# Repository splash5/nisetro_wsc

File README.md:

# nisetro_wsc
Capturing and perviewing WonderSwan Color screen/audio with カメレオンUSB FX2.

This project is based on カメレオンUSB FX2 http://optimize.ath.cx/cusb_fx2/index.html

What's inside this project:

eagle: Schematic, PCB and gerber file. (Design with EAGLE 9.6.2)

fx2lp: FX2LP uVision project.

max2: MAX2 Quartus project. (Develop with Quartus 13.0sp1 web edition)

preview: Preview software project. (Develop with Visual C++ Express 2010)

You will also need FX2LP SDK, SDL 2.0.14 and libsamplerate 0.2.1 to build/run preview software.

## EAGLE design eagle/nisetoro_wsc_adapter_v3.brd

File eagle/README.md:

This directory contains EAGLE schematic and board files for the nisetro_wsc.

The zip file is a gerber zipped file so you can build PCB with that.

I also uploaded the gerber zip file to [OSHPARK](https://oshpark.com/shared_projects/rcBuRHa7) so you can order PCB from there.

This version of adapter PCB removed two main buffer ICs so it should be much easier to build than previous version.

Also fixed the following problems:

 1. Screen will glitch after inserting first version (with cable) of headphone adapter.
 2. Device will be hard to turn on or off after inserting some type of cartridges.

 - BOM

|Part|Package|Value|Mouser|Qty|Note
|--|--|--|--|--|--|
|C7|C1206|10uF 16V|581-TAJA106K016RNJV|1|Tantalum Capacitors
|C8|C1206|100uF 4V|581-TAJA107K004RNJ|1|Tantalum Capacitors
|R1, R4|R0805|10K|603-RT0805FRE0710KL|2|
|R5|R0805|330|603-RT0805FRE07330RL|1|
|Q2|SOT-23-3|MMBT2222A|621-MMBT2222A-F|1| 
|U3|SOT-223-4|TLV1117-15CDCYR|595-TLV1117-15CDCYR|1|LDO for powering WSC (1.5V)
|CN3|||710-68712414022|1|FPC connector (Top contact)
|CN3 (alternative)|||710-68712414522|1|FPC connector (Bottom contact)
|R2, R3|R0805|10K|603-RT0805FRE0710KL|2| Optional if you want to install LED
|Q1|SOT-23-3|MMBT2222A|621-MMBT2222A-F|1| Optional if you want to install LED
|PWR|0603|Green LED|743-IN-S63BTG|1| Optional if you want to install LED. You can also choose the color you like, but make sure package is 0603.
||||710-687624100002|1|FPC cable (Same Side Contacts)
||||710-687724100002|1|FPC cable (Opposite Side Contacts)

U2 and C1 are for development purpose, please ignore them.

You will also need a 0.5mm pitch, 24pins FPC cable to connect from WSC CN2 (LCD connector) to adapter PCB CN3. The length should be at least 80mm long, or it will be very hard to install. I have tested with 150mm one and works ok, but if cable is too long the signal may not capture properly. The FPC cable also have two types: same side or opposite contacts. Choose one which makes installation easier, but **be sure that pin #1 of WSC CN2 connect to adapter board CN3 pin #1**, or you might damage your WSC or adapter board.

After soldering all the parts on the adapter PCB, it should looks like this: (Please ignore U2 and C1, that is for development purpose.)

Now you will need to connect at least RESET and BCLK to WSC to make everything work. LRCK, SDAT and SEN is for audio capturing. ON1 and ON2 are optional if you want to install a tactile switch as power switch. "TO WSC" is 1.5V output, connect V1 and VS to WSC power supply module V1 and VS pin.

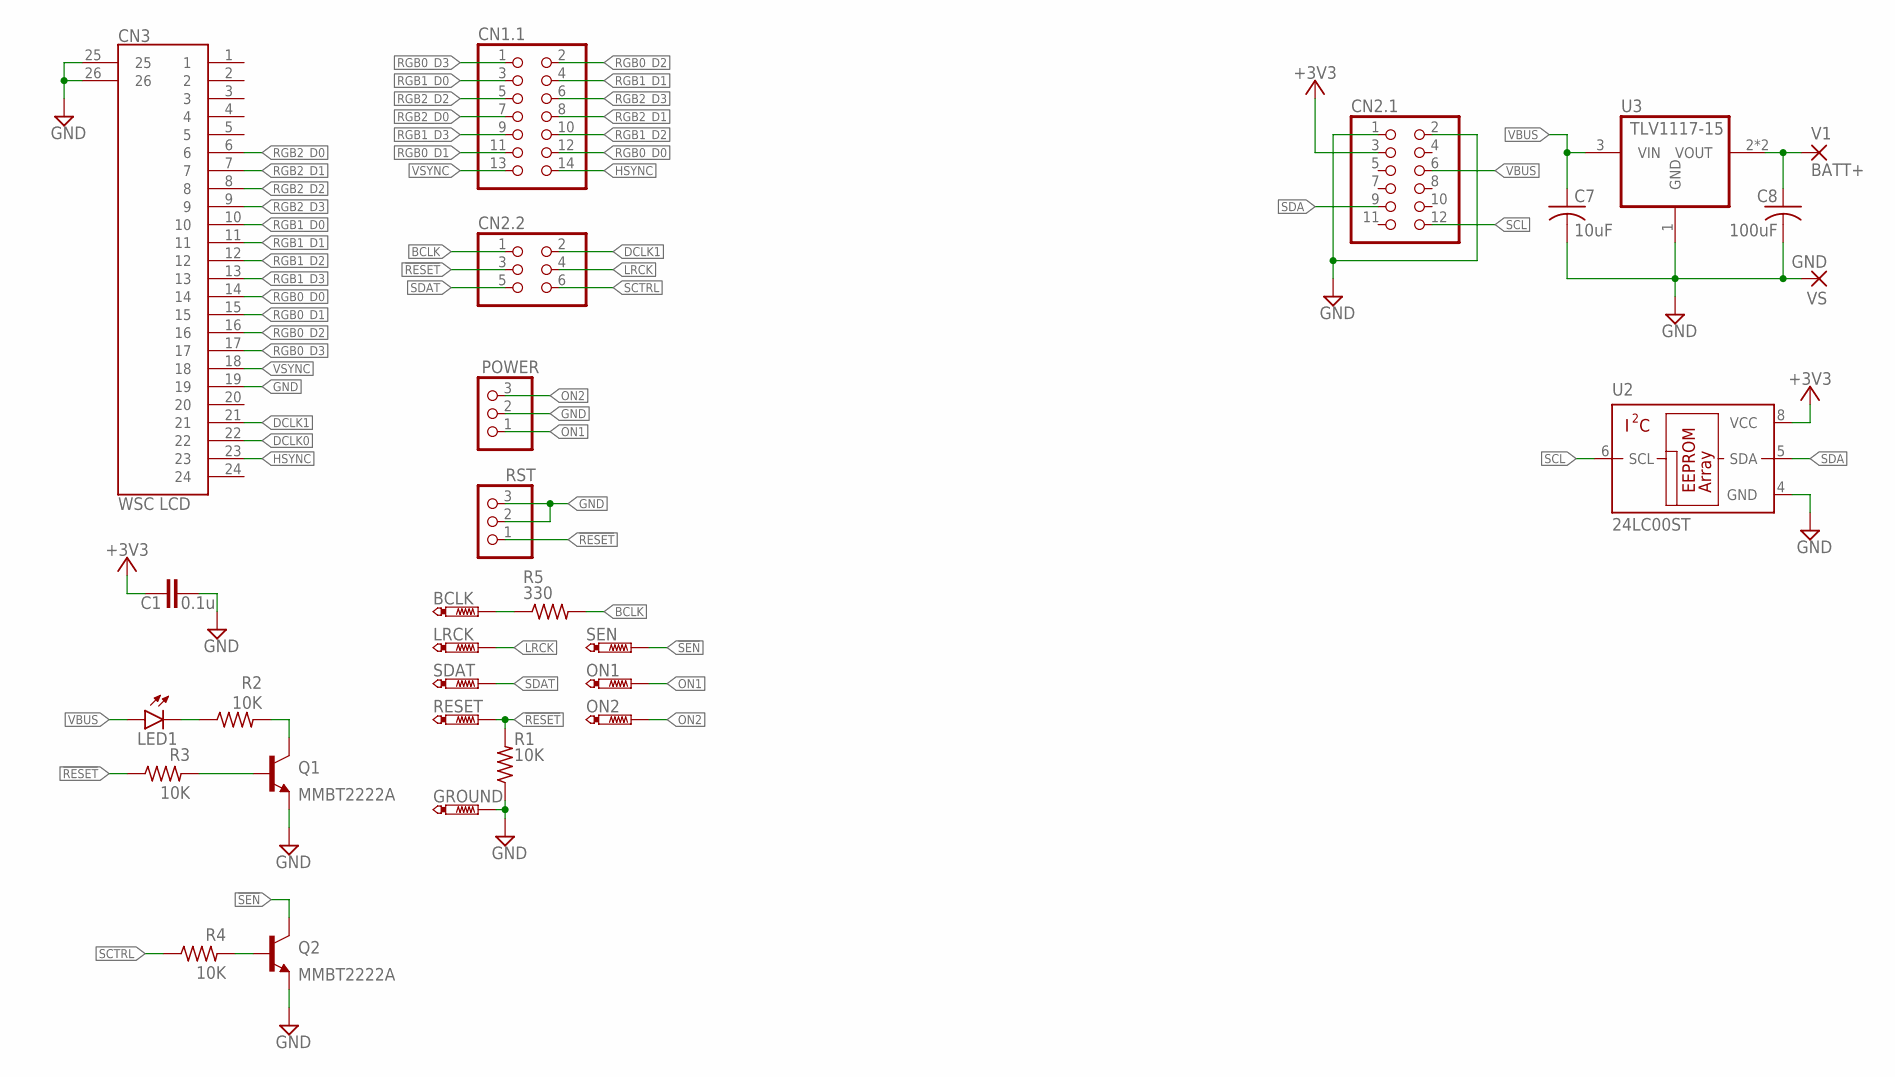
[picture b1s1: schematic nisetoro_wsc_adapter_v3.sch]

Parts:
BCLK: PTR1B1,27; B1,27
C1: 0.1u; C0805
C7: 10uF; C1210
C8: 100uF; C1210
CN1.1: PINHD-2X7; 2X07
CN2.1: PINHD-2X6; 2X06
CN2.2: PINHD-2X3; 2X03
CN3: WSC LCD; 68712414022/R
GROUND: PTR1B1,27; B1,27
LED1: LEDSML0603; SML0603
LRCK: PTR1B1,27; B1,27
ON1, ON2: PTR1B1,27; B1,27
POWER: PINHD-1X3/ROUND; 1X03/ROUND
Q1, Q2: MMBT2222A; SOT23-BEC
R1, R2, R3, R4: 10K; R0805
R5: 330; R0805
RESET: PTR1B1,27; B1,27
RST: PINHD-1X3/ROUND; 1X03/ROUND
SDAT: PTR1B1,27; B1,27
SEN: PTR1B1,27; B1,27
U2: 24LC00ST; TSSOP8
U3: TLV1117-15; SOT223
V1: BATT+; SMD2,54-5,08
VS: GND; SMD2,54-5,08

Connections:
!RESET: CN2.2.3, R1.2, R3.1, RESET.TP, RST.1
!SEN: Q2.C, SEN.TP
+3V3: C1.1, CN2.1.3, U2.8 (VCC)
BATT+: C8.1, U3.2 (VOUT), U3.4 (VOUT), V1.1
BCLK: CN2.2.1, R5.2
DCLK0: CN3.22
DCLK1: CN2.2.2, CN3.21
GND: C1.2, C7.2, C8.2, CN2.1.1, CN2.1.2, CN3.19, CN3.25, CN3.26, GROUND.TP, POWER.2, Q1.E, Q2.E, R1.1, RST.2, RST.3, U2.4 (GND), U3.1 (GND), VS.1
HSYNC: CN1.1.14, CN3.23
LRCK: CN2.2.4, LRCK.TP
unnamed: LED1.C, R2.1
unnamed: Q1.C, R2.2
unnamed: BCLK.TP, R5.1
unnamed: Q1.B, R3.2
unnamed: Q2.B, R4.2
ON1: ON1.TP, POWER.1
ON2: ON2.TP, POWER.3
RGB0_D0: CN1.1.12, CN3.14
RGB0_D1: CN1.1.11, CN3.15
RGB0_D2: CN1.1.2, CN3.16
RGB0_D3: CN1.1.1, CN3.17
RGB1_D0: CN1.1.3, CN3.10
RGB1_D1: CN1.1.4, CN3.11
RGB1_D2: CN1.1.10, CN3.12
RGB1_D3: CN1.1.9, CN3.13
RGB2_D0: CN1.1.7, CN3.6
RGB2_D1: CN1.1.8, CN3.7
RGB2_D2: CN1.1.5, CN3.8
RGB2_D3: CN1.1.6, CN3.9
SCL: CN2.1.12, U2.6 (SCL)
SCTRL: CN2.2.6, R4.1
SDA: CN2.1.9, U2.5 (SDA)
SDAT: CN2.2.5, SDAT.TP
VBUS: C7.1, CN2.1.6, LED1.A, U3.3 (VIN)
VSYNC: CN1.1.13, CN3.18

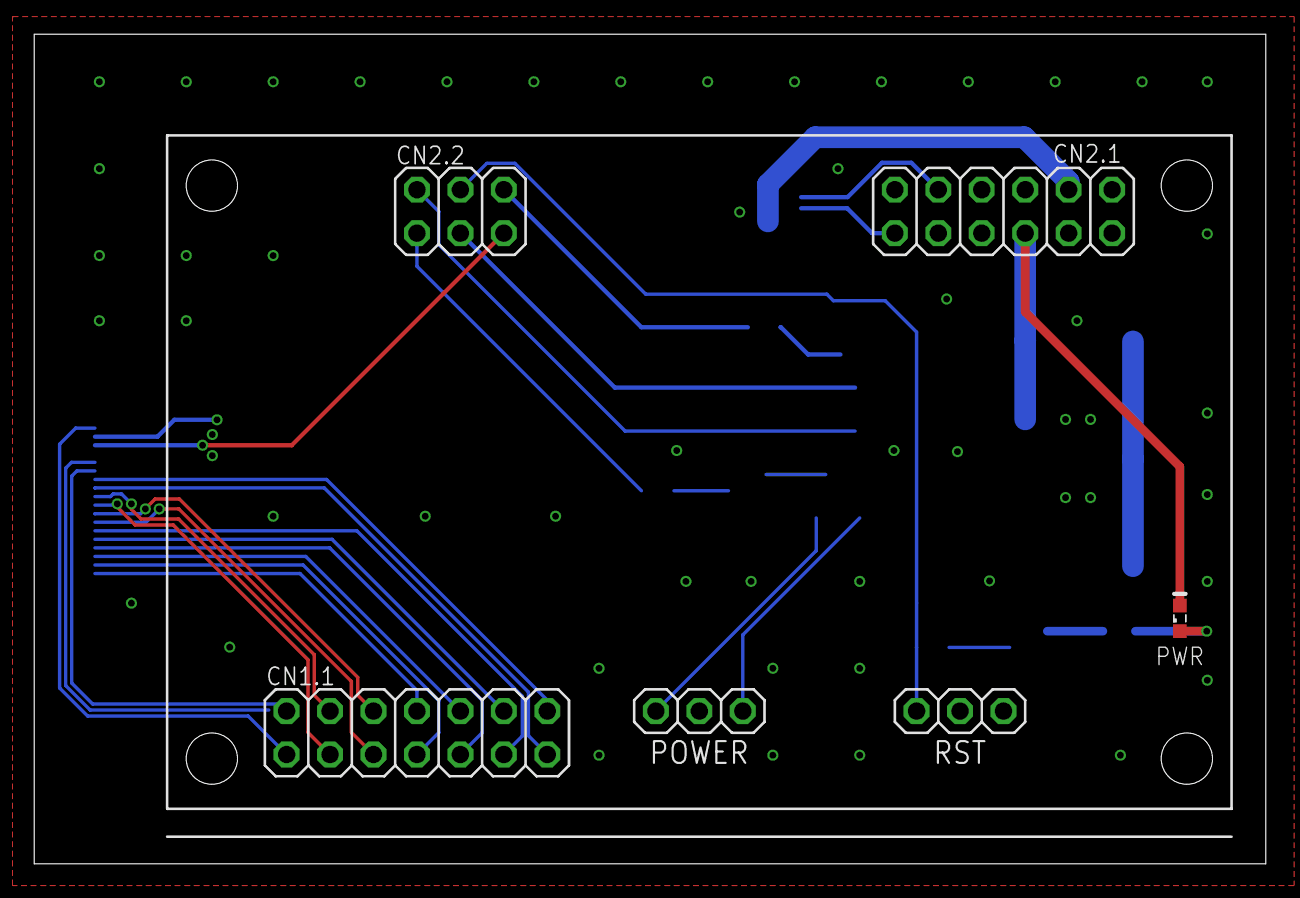
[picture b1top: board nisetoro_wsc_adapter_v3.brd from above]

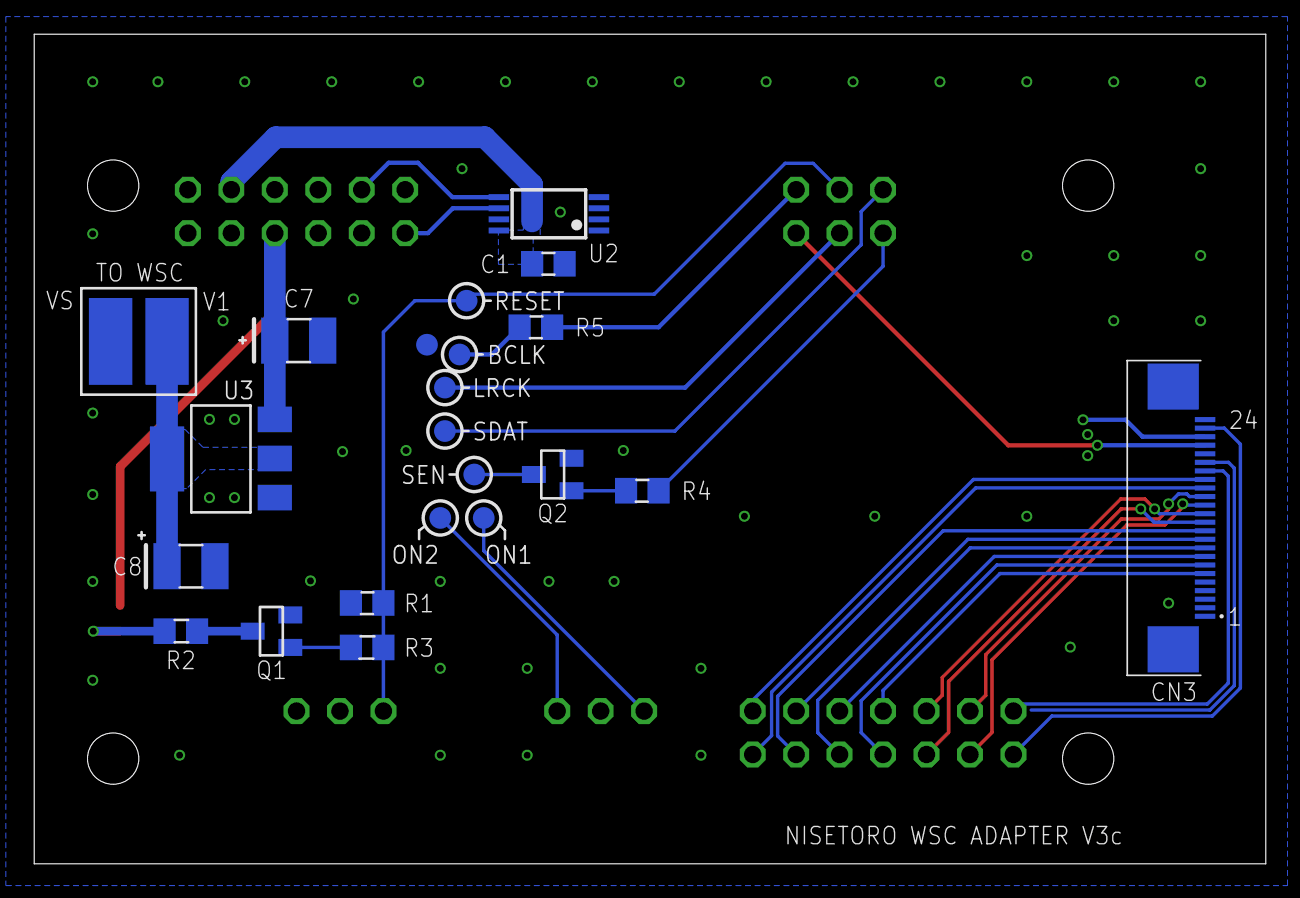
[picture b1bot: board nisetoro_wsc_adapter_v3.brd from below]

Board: 2 copper layers, 72.0 x 48.5 mm, 29 parts (23 on the bottom side), 34 nets.

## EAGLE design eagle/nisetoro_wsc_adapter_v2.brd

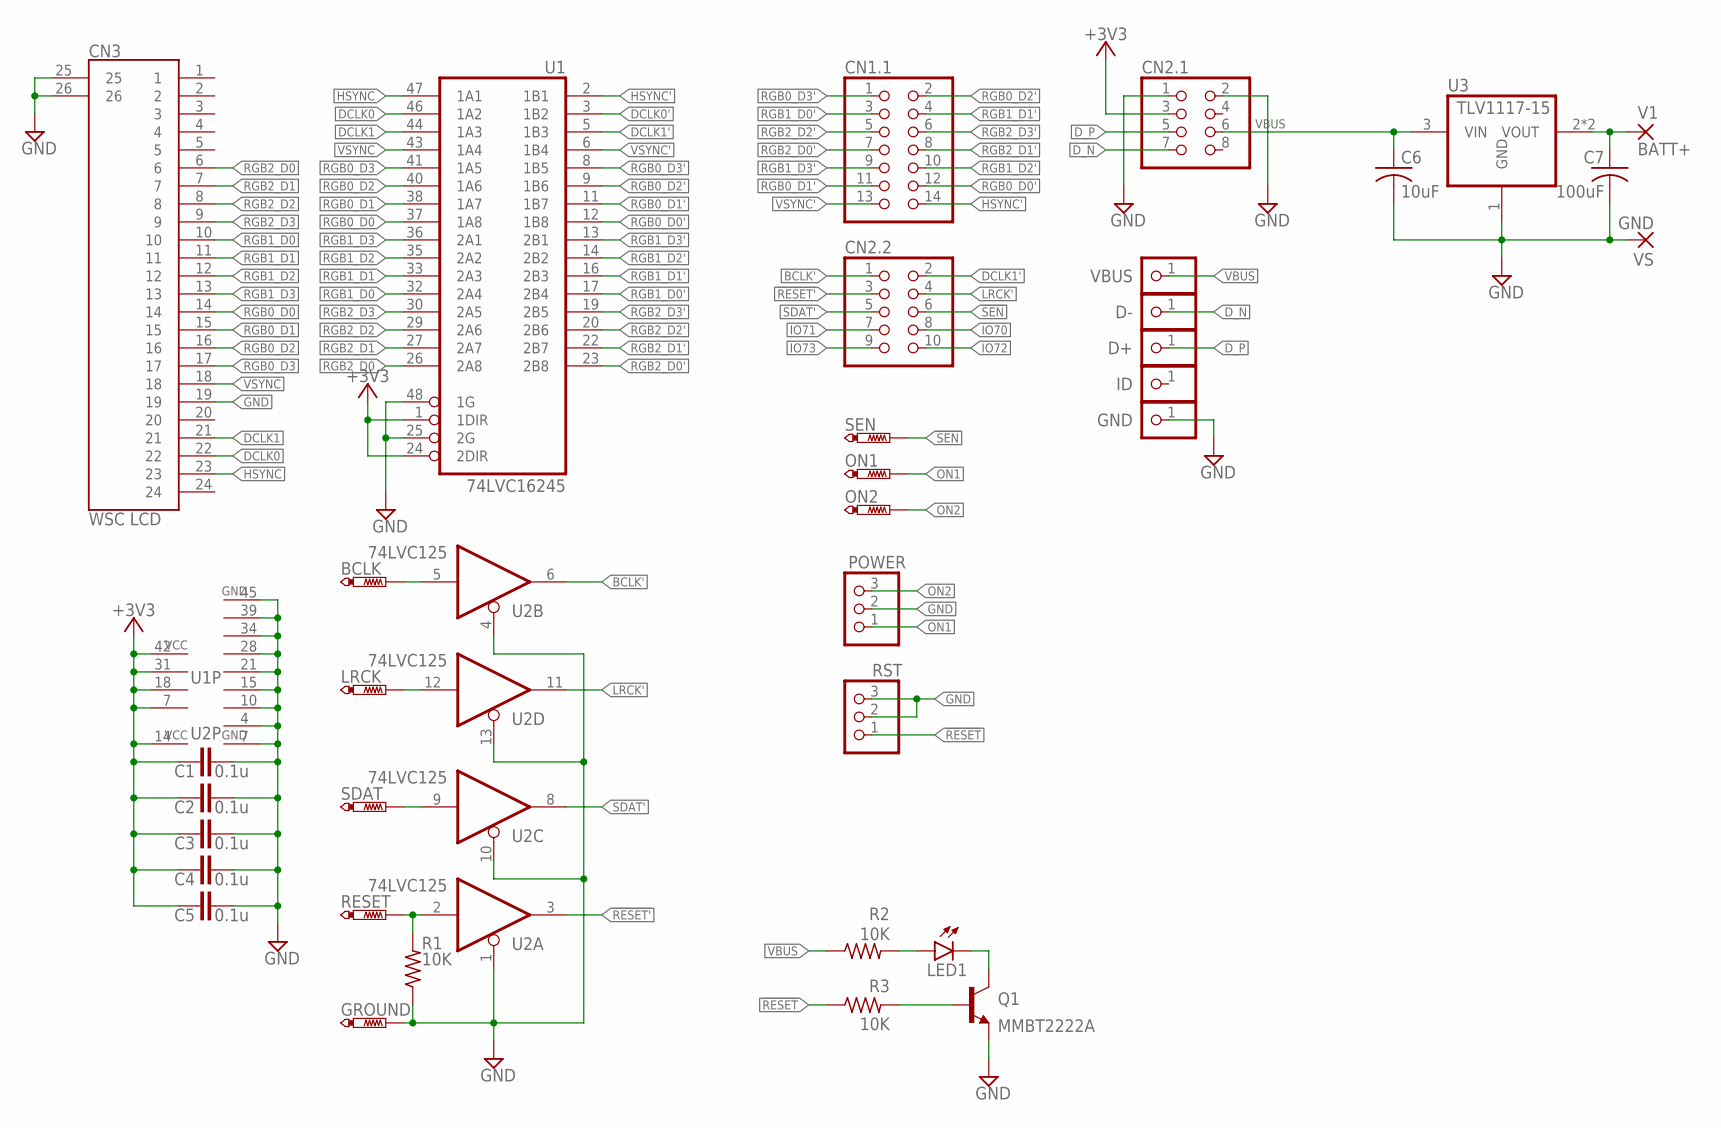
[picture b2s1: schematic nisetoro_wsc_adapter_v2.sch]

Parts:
BCLK: PTR1B1,27; B1,27
C1, C2, C3, C4, C5: 0.1u; C0603
C6: 10uF; C1210
C7: 100uF; C1210
CN1.1: PINHD-2X7; 2X07
CN2.1: PINHD-2X4; 2X04
CN2.2: PINHD-2X5; 2X05
CN3: WSC LCD; 68712414022/R
D+: PINHD-1X1; 1X01
D-: PINHD-1X1; 1X01
GND: PINHD-1X1; 1X01
GROUND: PTR1B1,27; B1,27
ID: PINHD-1X1; 1X01
LED1: LEDSML0603; SML0603
LRCK: PTR1B1,27; B1,27
ON1, ON2: PTR1B1,27; B1,27
POWER: PINHD-1X3/ROUND; 1X03/ROUND
Q1: MMBT2222A; SOT23-BEC
R1, R2, R3: 10K; R0603
RESET: PTR1B1,27; B1,27
RST: PINHD-1X3/ROUND; 1X03/ROUND
SDAT: PTR1B1,27; B1,27
SEN: PTR1B1,27; B1,27
U1: 74LVC16245; TSSOP48
U2: 74LVC125; TSSOP14
U3: TLV1117-15; SOT223
V1: BATT+; SMD2,54-5,08
VBUS: PINHD-1X1; 1X01
VS: GND; SMD2,54-5,08

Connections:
!RESET: R1.2, R3.1, RESET.TP, RST.1, U2.2 (I)
!RESET': CN2.2.3, U2.3 (O)
!SEN: CN2.2.6, SEN.TP
+3V3: C1.1, C2.1, C3.1, C4.1, C5.1, CN2.1.3, U1.1 (1DIR), U1.7 (VCC), U1.18 (VCC), U1.24 (2DIR), U1.31 (VCC), U1.42 (VCC), U2.14 (VCC)
BATT+: C7.1, U3.2 (VOUT), U3.4 (VOUT), V1.1
BCLK: BCLK.TP, U2.5 (I)
BCLK': CN2.2.1, U2.6 (O)
DCLK0: CN3.22, U1.46 (1A2)
DCLK0': U1.3 (1B2)
DCLK1: CN3.21, U1.44 (1A3)
DCLK1': CN2.2.2, U1.5 (1B3)
D_N: CN2.1.7, D-.1
D_P: CN2.1.5, D+.1
GND: C1.2, C2.2, C3.2, C4.2, C5.2, C6.2, C7.2, CN2.1.1, CN2.1.2, CN3.19, CN3.25, CN3.26, GND.1, GROUND.TP, POWER.2, Q1.E, R1.1, RST.2, RST.3, U1.4 (GND), U1.10 (GND), U1.15 (GND), U1.21 (GND), U1.25 (2G), U1.28 (GND), U1.34 (GND), U1.39 (GND), U1.45 (GND), U1.48 (1G), U2.1 (OE), U2.4 (OE), U2.7 (GND), U2.10 (OE), U2.13 (OE), U3.1 (GND), VS.1
HSYNC: CN3.23, U1.47 (1A1)
HSYNC': CN1.1.14, U1.2 (1B1)
IO70: CN2.2.8
IO71: CN2.2.7
IO72: CN2.2.10
IO73: CN2.2.9
LRCK: LRCK.TP, U2.12 (I)
LRCK': CN2.2.4, U2.11 (O)
unnamed: LED1.A, R2.2
unnamed: LED1.C, Q1.C
unnamed: Q1.B, R3.2
ON1: ON1.TP, POWER.1
ON2: ON2.TP, POWER.3
RGB0_D0: CN3.14, U1.37 (1A8)
RGB0_D0': CN1.1.12, U1.12 (1B8)
RGB0_D1: CN3.15, U1.38 (1A7)
RGB0_D1': CN1.1.11, U1.11 (1B7)
RGB0_D2: CN3.16, U1.40 (1A6)
RGB0_D2': CN1.1.2, U1.9 (1B6)
RGB0_D3: CN3.17, U1.41 (1A5)
RGB0_D3': CN1.1.1, U1.8 (1B5)
RGB1_D0: CN3.10, U1.32 (2A4)
RGB1_D0': CN1.1.3, U1.17 (2B4)
RGB1_D1: CN3.11, U1.33 (2A3)
RGB1_D1': CN1.1.4, U1.16 (2B3)
RGB1_D2: CN3.12, U1.35 (2A2)
RGB1_D2': CN1.1.10, U1.14 (2B2)
RGB1_D3: CN3.13, U1.36 (2A1)
RGB1_D3': CN1.1.9, U1.13 (2B1)
RGB2_D0: CN3.6, U1.26 (2A8)
RGB2_D0': CN1.1.7, U1.23 (2B8)
RGB2_D1: CN3.7, U1.27 (2A7)
RGB2_D1': CN1.1.8, U1.22 (2B7)
RGB2_D2: CN3.8, U1.29 (2A6)
RGB2_D2': CN1.1.5, U1.20 (2B6)
RGB2_D3: CN3.9, U1.30 (2A5)
RGB2_D3': CN1.1.6, U1.19 (2B5)
SDAT: SDAT.TP, U2.9 (I)
SDAT': CN2.2.5, U2.8 (O)
VBUS: C6.1, CN2.1.6, R2.1, U3.3 (VIN), VBUS.1
VSYNC: CN3.18, U1.43 (1A4)
VSYNC': CN1.1.13, U1.6 (1B4)

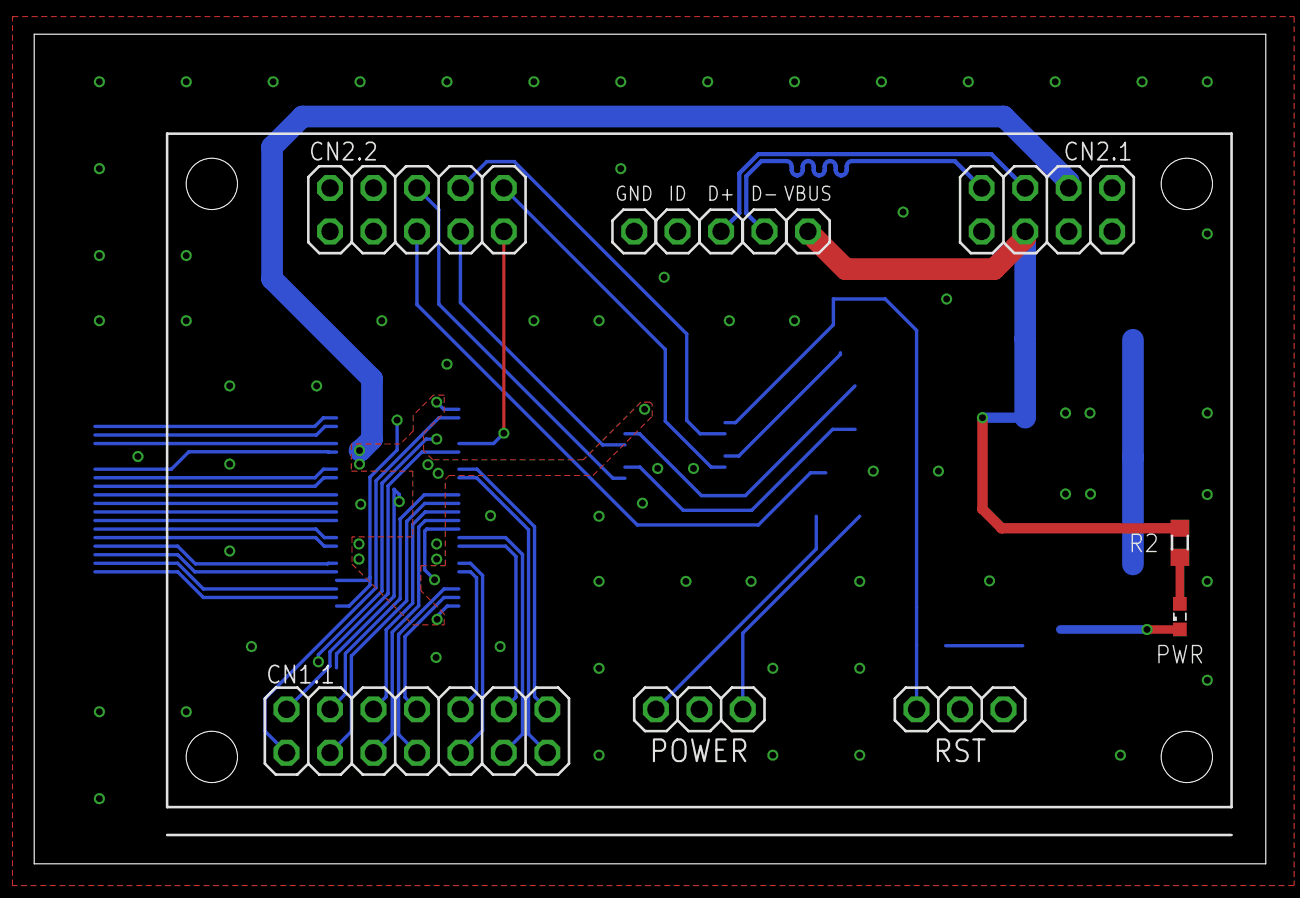
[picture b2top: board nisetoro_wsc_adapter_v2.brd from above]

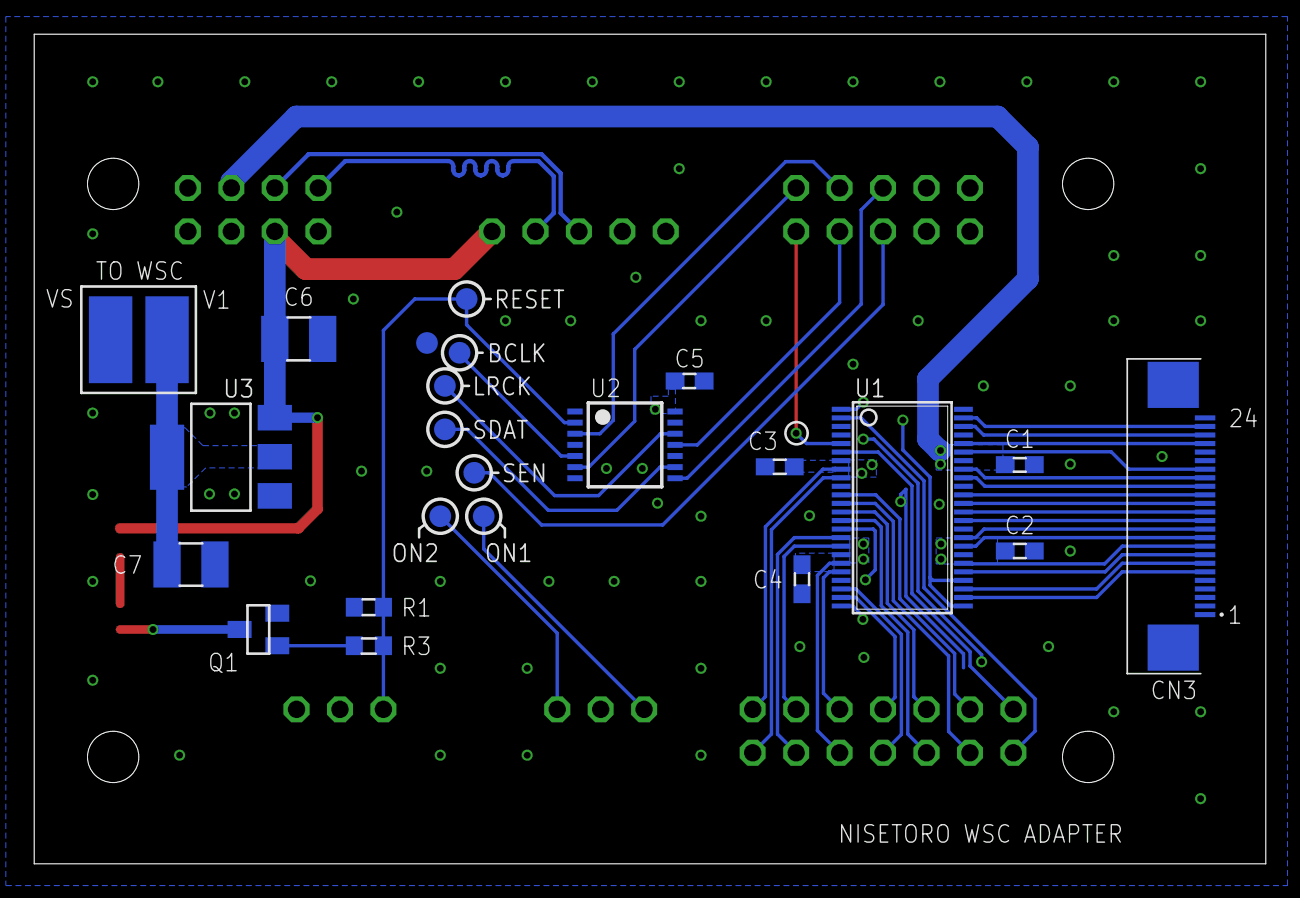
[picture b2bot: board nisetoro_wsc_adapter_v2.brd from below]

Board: 2 copper layers, 72.0 x 48.5 mm, 36 parts (24 on the bottom side), 51 nets.

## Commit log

2021-06-24 Add fx2lp firmware project
    Add max2 project
2021-06-28 Add preview software project
2021-06-28 Add schematic, board and gerber files
2021-06-28 Use new method for capturing I2S data
2021-06-28 Very simple readme, will writing more details later
2021-06-29 Add README.md in eagle directory
2021-06-29 Update image URL
2021-06-29 [Preview] Add texture scale mode
2021-06-30 Change render surface format to ARGB8888
    Reduce audio playback buffer to 1024 frames
2021-06-30 Add README.md about max2
2021-06-30 Add segment surface for future LCD segment drawing
2021-07-04 Update solder point diagram
2021-07-07 Add menu for setting backbuffer size and texture scaling mode
2021-07-08 Implement LCD segment rendering
2021-07-09 Fix kerorican rotation
2021-07-10 Workaround for vbo error message
2021-11-22 Add photo
2022-07-12 Update README.md
    Correct mouser part ID for U1 (thx to @SatoDen_MO)
2022-07-21 Update README.md
    Correct Mouser part no. of C1 to C5.
2023-01-23 Update adapter PCB to v3b
2023-01-23 Resize v3 pcb image
2023-02-20 EAGLE: Update adapter PCB to V3c
    PREVIEW: Fix sound icon
    MAX2: Set audio reg default value to 1 to match new version PCB
2023-02-22 Add png file of adapter schematic
